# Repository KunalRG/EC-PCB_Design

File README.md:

# EC-PCB_Design
This project focuses on designing PCB for water level indication
In the field of electronics it is very important to design and create your own PCB(Printed Circuit Board).PCB help to optimise your circuit connections.
There is huge demand of designing a small sized PCB in the field of robotics,microcontroller,etc.
So,I hope this project will help to understand basics of designing PCB.
Thank you and keep leaning.

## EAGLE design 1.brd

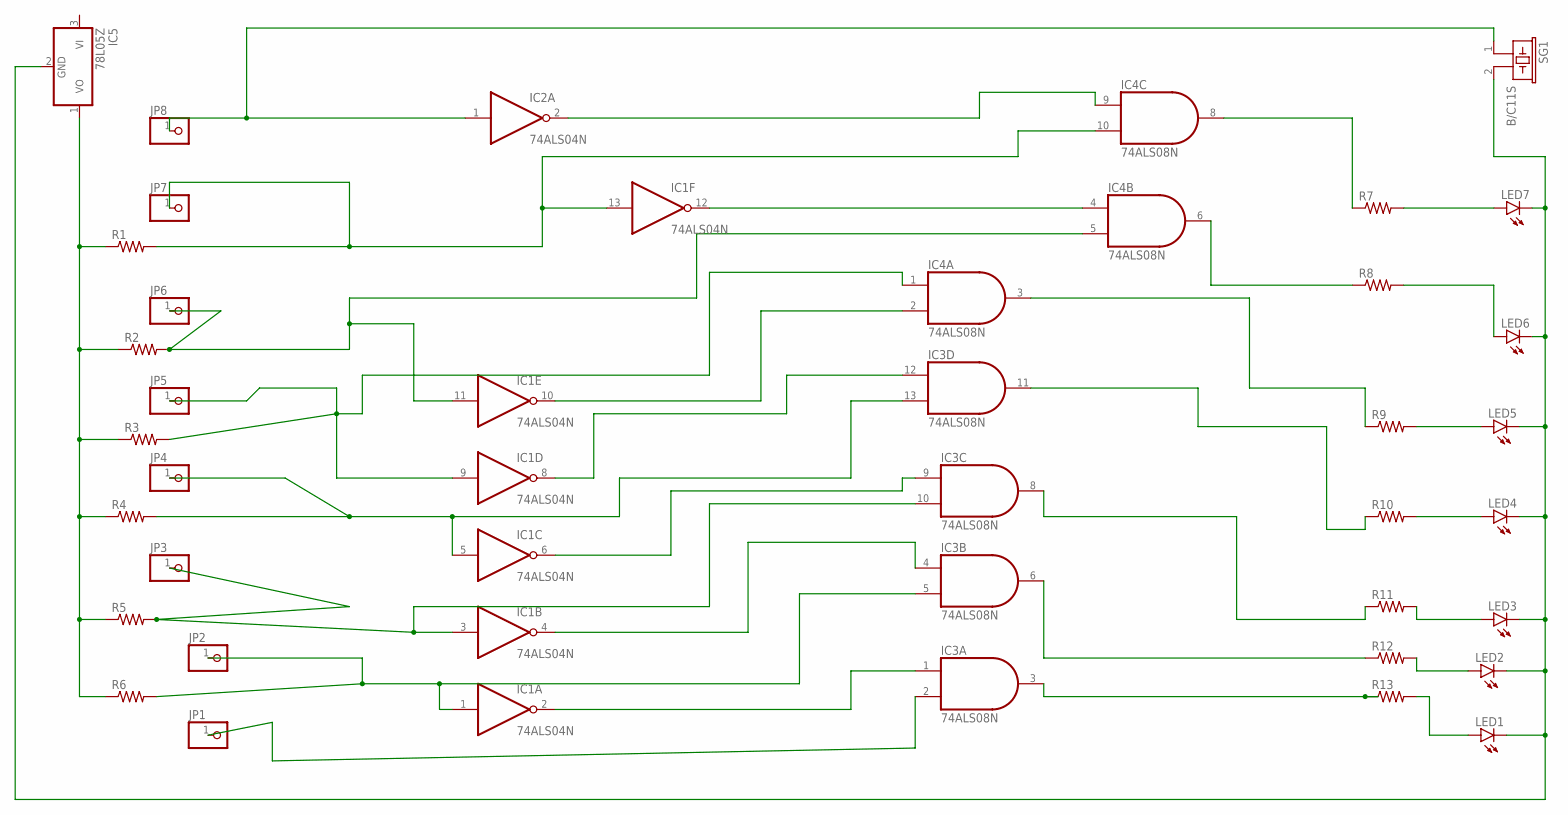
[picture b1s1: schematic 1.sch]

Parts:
IC1, IC2: 74ALS04N; DIL14
IC3, IC4: 74ALS08N; DIL14
IC5: 78L05Z; TO92
JP1, JP2, JP3, JP4, JP5, JP6, JP7, JP8: PINHD-1X1; 1X01
LED1, LED2, LED3, LED4, LED5, LED6, LED7: LED10MM
R1, R2, R3, R4, R5, R6, R7, R8, R9, R10, R11, R12, R13: R-US_0204/5; 0204/5
SG1: B/C11S

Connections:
GND: IC1.7 (GND), IC2.7 (GND), IC3.7 (GND), IC4.7 (GND)
unnamed: IC1.1 (I), IC3.5 (I1), JP2.1, R6.2
unnamed: IC1.3 (I), IC3.10 (I1), JP3.1, R5.2
unnamed: IC1.5 (I), IC3.13 (I1), JP4.1, R4.2
unnamed: IC1.9 (I), IC4.1 (I0), JP5.1, R3.2
unnamed: IC1.11 (I), IC4.5 (I1), JP6.1, R2.2
unnamed: IC1.13 (I), IC4.10 (I1), JP7.1, R1.2
unnamed: IC1.2 (O), IC3.1 (I0)
unnamed: IC1.4 (O), IC3.4 (I0)
unnamed: IC1.6 (O), IC3.9 (I0)
unnamed: IC1.8 (O), IC3.12 (I0)
unnamed: IC1.10 (O), IC4.2 (I1)
unnamed: IC1.12 (O), IC4.4 (I0)
unnamed: IC3.2 (I1), JP1.1
unnamed: IC3.3 (O), R13.1
unnamed: IC4.8 (O), R7.1
unnamed: IC3.11 (O), R10.1
unnamed: IC4.3 (O), R9.1
unnamed: IC2.2 (O), IC4.9 (I0)
unnamed: IC3.8 (O), R11.1
unnamed: IC3.6 (O), R12.1
unnamed: IC2.1 (I), JP8.1, SG1.1
unnamed: IC4.6 (O), R8.1
unnamed: LED1.A, R13.2
unnamed: LED2.A, R12.2
unnamed: LED3.A, R11.2
unnamed: LED4.A, R10.2
unnamed: LED5.A, R9.2
unnamed: LED6.A, R8.2
unnamed: LED7.A, R7.2
unnamed: IC5.1 (VO), R1.1, R2.1, R3.1, R4.1, R5.1, R6.1
unnamed: IC5.2 (GND), LED1.K (C), LED2.K (C), LED3.K (C), LED4.K (C), LED5.K (C), LED6.K (C), LED7.K (C), SG1.2
VCC: IC1.14 (VCC), IC2.14 (VCC), IC3.14 (VCC), IC4.14 (VCC)

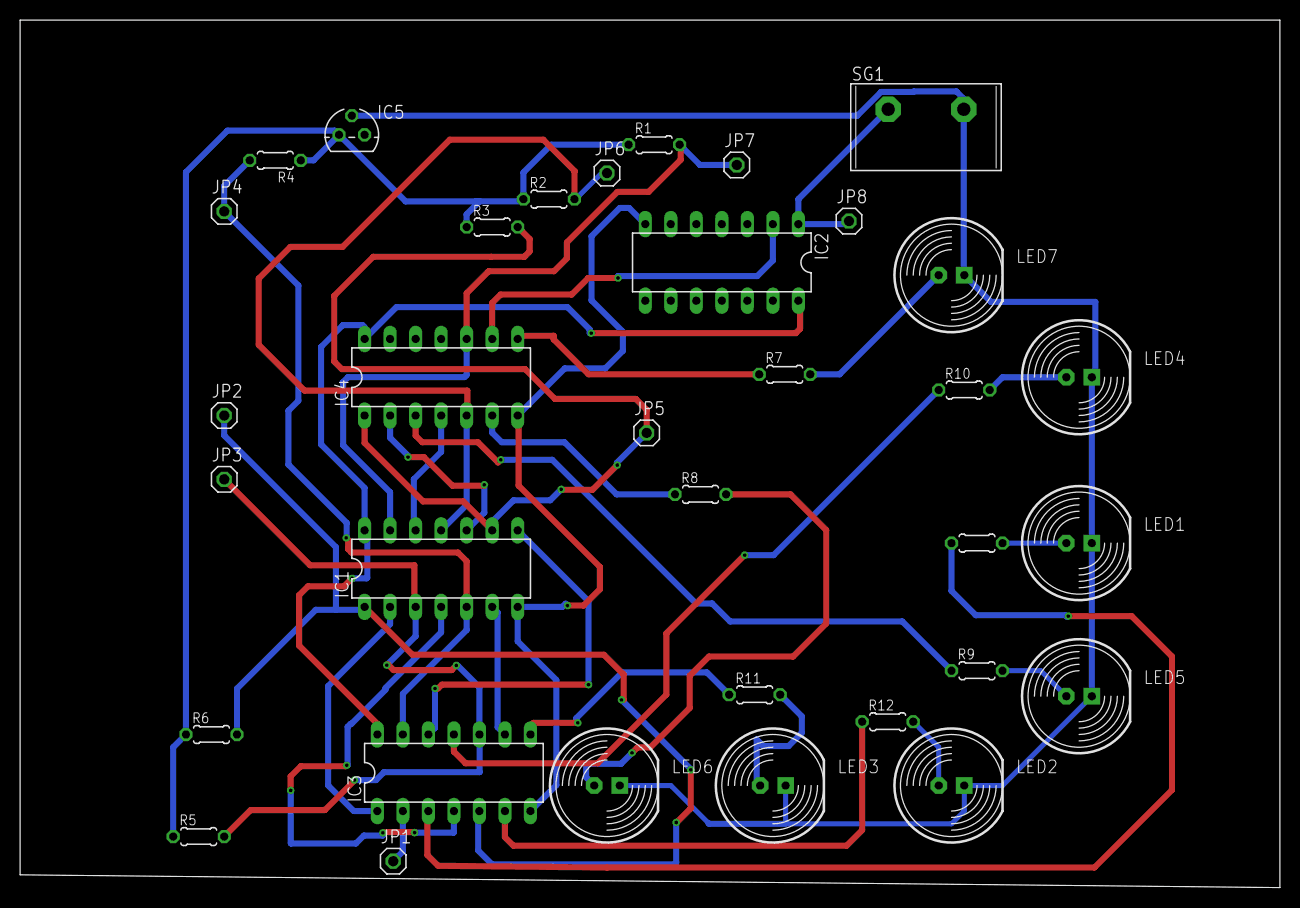
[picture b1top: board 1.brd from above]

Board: 2 copper layers, 125.4 x 86.3 mm, 34 parts (0 on the bottom side), 33 nets.

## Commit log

2020-08-03 Initial commit:Actual board
2020-08-03 All output of designs
